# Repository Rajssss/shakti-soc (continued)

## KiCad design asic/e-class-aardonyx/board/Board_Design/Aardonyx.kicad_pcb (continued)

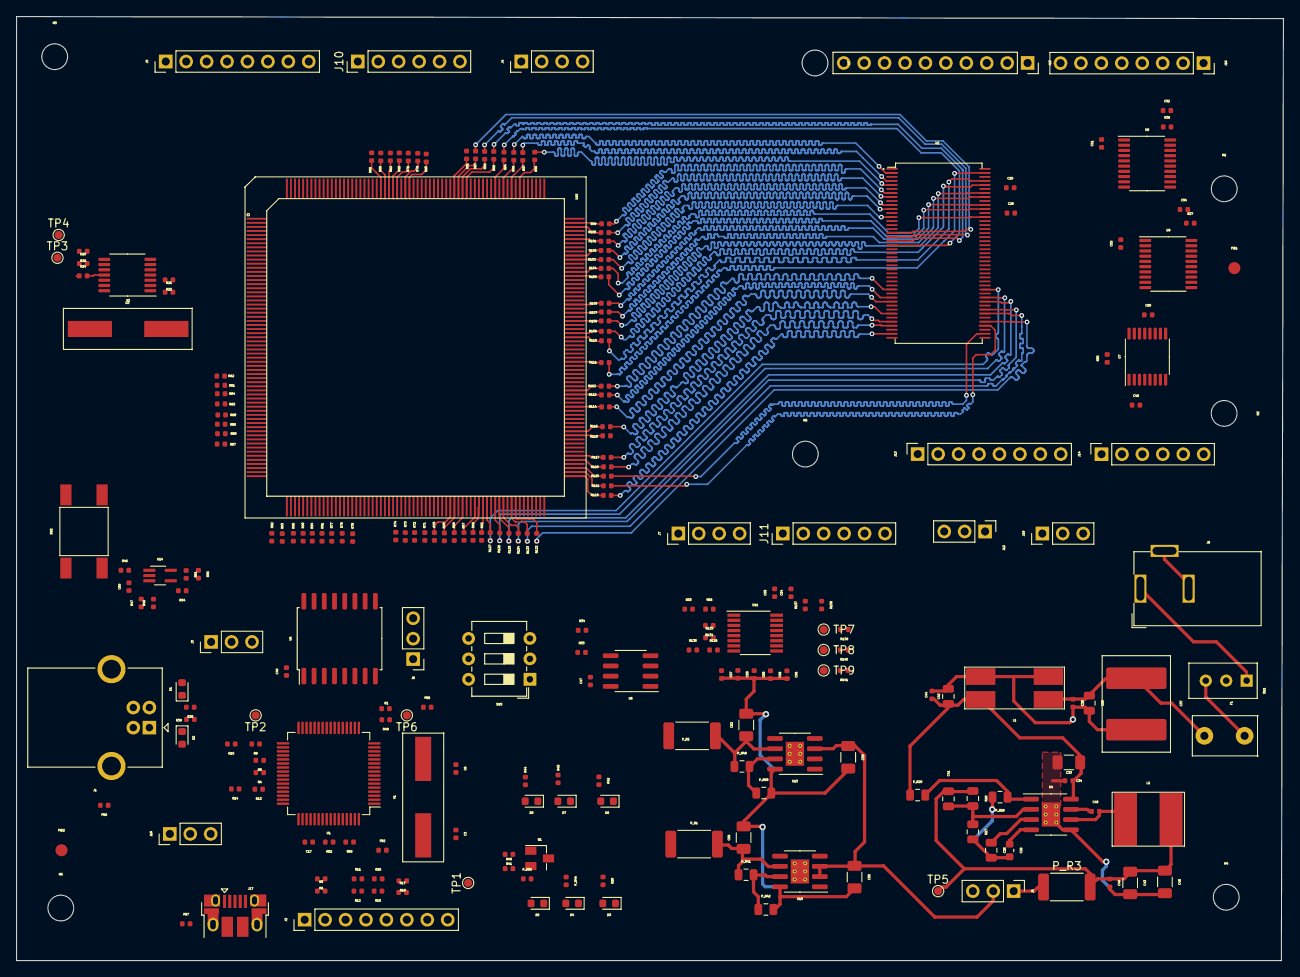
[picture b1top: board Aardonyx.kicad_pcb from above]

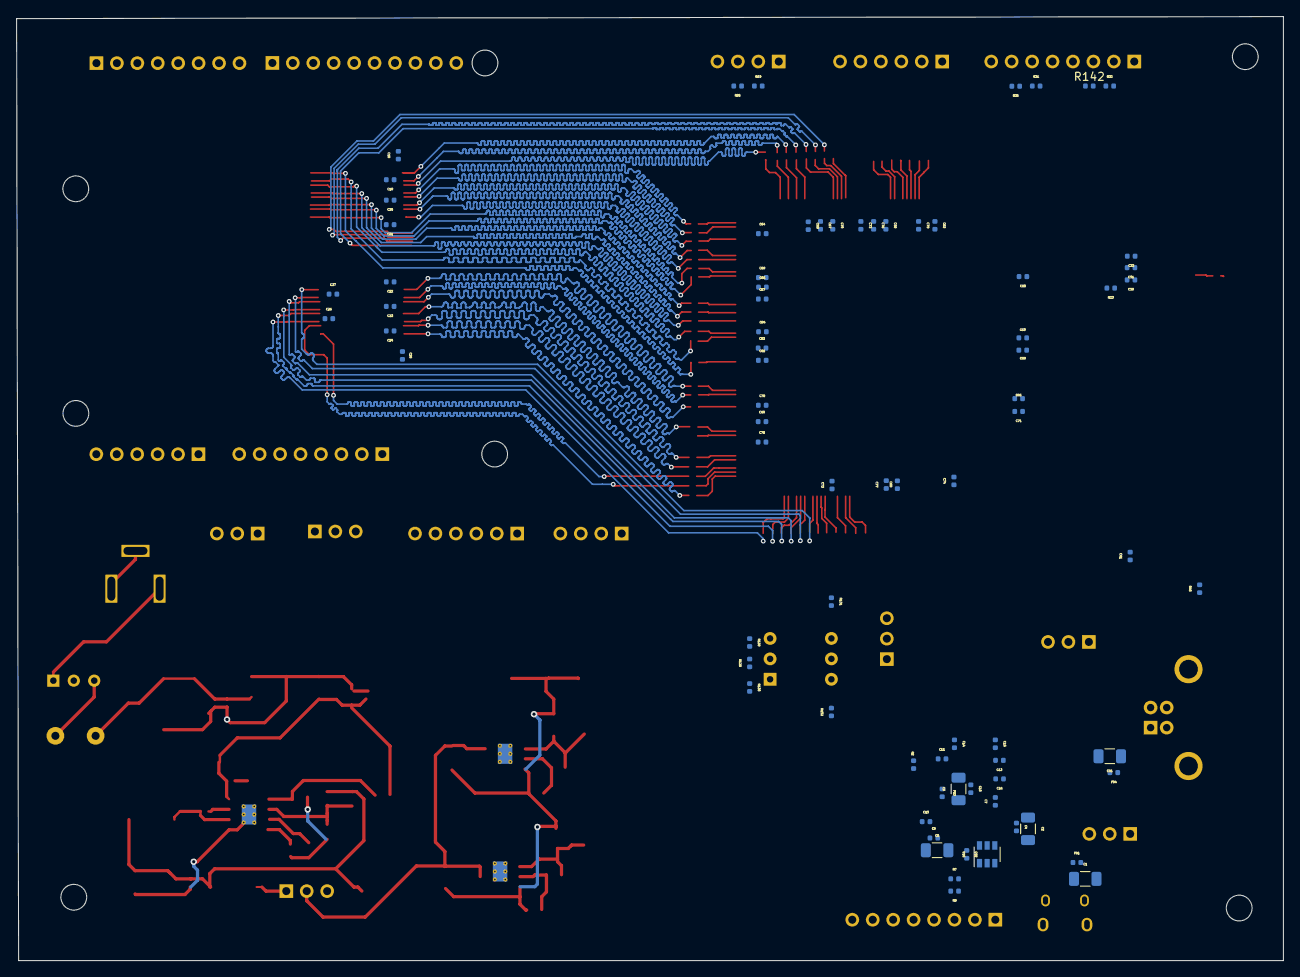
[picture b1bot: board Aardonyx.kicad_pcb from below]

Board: 4 copper layers, 157.5 x 117.3 mm, 325 parts (77 on the bottom side), 287 nets.

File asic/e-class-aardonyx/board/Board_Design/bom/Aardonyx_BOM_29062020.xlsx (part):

Reference | Value | FootPrint | Datasheet | Description | Digikey Part number | Manufaturer Part Number | Manufaturer | Qty
> C3, C6 | 18PF,0402 | Capacitor_SMD:C_0402_1005Metric | https://www.digikey.in/product-detail/en/yageo/CC0201JRNPO9B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 | CAP CER 18PF 50V C0G/NPO 0201 | 311-1386-1-ND | CC0201JRNPO9BN180 | Yageo | 2
> C1, C2, C5, C9, C55, C59, C91 | 4.7UF,1206 | Capacitor_SMD:C_1206_3216Metric | https://www.digikey.in/product-detail/en/kemet/T491A475K016A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 | CAP TANT 4.7UF 10% 16V 1206 | 399-18027-1-ND | T491A475K016AT | Kemet | 7
> C4, C7, C8, C10-C32, C34, C39, C40, C44, C46-C54, C57, C58, C60, C61, C63-C90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 | 0.1UF,0402 | Capacitor_SMD:C_0402_1005Metric | https://www.digikey.in/product-detail/en/avx-corporation/040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 | CAP CER 0.1UF 25V X7R 0402 | 478-10050-1-ND | 04023C104JAT2A | AVX Corporation | 76
> C35, C38, C42 | 1UF,0805 | Capacitor_SMD:C_0805_2012Metric | https://www.digikey.in/product-detail/en/kemet/C0805C105J3RA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 | CAP CER 1UF 25V X7R 0805 | 399-10060-6-ND | C0805C105J3RACTU | Kemet | 3
C36 | 7500PF,0603 | Capacitor_SMD:C_0603_1608Metric | https://www.digikey.in/product-detail/en/kemet/C0603C752J3GA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 | CAP CER 7500PF 25V C0G/NP0 0603 | 399-9980-1-ND | C0603C752J3GAC7867 | Kemet | 1
C37 | 220UF,2924 | Aardonyx:CP_EIA-7260-38_VISHAY_Pad2.68x7.50mm_HandSolder | https://www.digikey.com/product-detail/en/avx-corporation/TC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 | CAP TANT POLY 220UF 25V 2924 | 478-12518-1-ND | TCN4227M025R0100 | AVX Corporation | 1
C41 | 15PF,0805 | Capacitor_SMD:C_0805_2012Metric | https://www.digikey.in/product-detail/en/w%C3%BCrth-elektron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 | CAP CER 15PF 25V C0G/NP0 0805 | 732-7828-1-ND | 885012007029 | Wurth Elektronik | 1
> C33, C43, C45 | 22UF,1206 | Capacitor_SMD:C_1206_3216Metric | https://www.digikey.in/product-detail/en/samsung-electro-mec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 | CAP CER 22UF 25V X5R 1206 | 1276-3047-1-ND | CL31A226KAHNNNE | Samsung Electro-Mechanics | 3
> C56, C62 | 10UF,1206 | Capacitor_SMD:C_1206_3216Metric | https://www.digikey.in/product-detail/en/kemet/C1206C106J3RA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 | CAP CER 10UF 25V X7R 1206 | 399-15734-1-ND | C1206C106J3RACAUTO | KEMET | 2
> D1, D2 | CG0603MLC-12E | Diode_SMD:D_0603_1608Metric | https://www.bourns.com/docs/Product-Datasheets/MLC.pdf | VARISTOR 0603 | CG0603MLC-12ECT-ND | CG0603MLC-12E | Bourns Inc. | 2
> D3-D8 | LED,1206 | LED_SMD:LED_0603_1608Metric | https://www.digikey.com/product-detail/en/lumex-opto-compone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 | LED GREEN DIFFUSED 1206 SMD | 67-1002-1-ND | SML-LX1206GW-TR | Lumex Opto/Components Inc. | 6
F1 | PTCCL13H921DBE | Aardonyx:vishay_ptccl_d1mm_w5mm | https://www.digikey.in/products/en?keywords=PTCCL13H921DBE | PTC RESET FUSE 30V 920MA RADIAL | BC2323-ND | PTCCL13H921DBE | Vishay BC Components | 1
> FB1-FB5 | 600E,FB,0402 | Inductor_SMD:L_0402_1005Metric | https://www.digikey.in/product-detail/en/w%C3%BCrth-elektron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 | FERRITE BEAD 600 OHM 0402 1LN | 732-2388-1-ND | 7427927291 | Wurth Elektronik | 5
> FB6, FB7 | 47E,FB,0402 | Inductor_SMD:L_0402_1005Metric | https://www.digikey.in/product-detail/en/w%C3%BCrth-elektron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 | FERRITE BEAD 47 OHM 0603 1LN | 732-1596-1-ND | 742792608 | Wurth Elektronik | 2
> FID1, FID2 | Fiducial | Fiducial:Fiducial_1.5mm_Mask3mm | ~ |  |  |  |  | 2
> H1-H7 | MountingHole | MountingHole:MountingHole_3.2mm_M3 | ~ |  |  |  |  | 7
J1 | USB_B_6PIN | Connector_USB:USB_B_OST_USB-B1HSxx_Horizontal | https://www.digikey.com/product-detail/en/amphenol-icc-fci/6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 | CONN RCPT USB2.0 TYPEB 4POS R/A | 609-1039-ND | 61729-0010BLF | Amphenol ICC (FCI) | 1
> J2, J9 | Conn_1x8 | Connector_PinHeader_2.54mm:PinHeader_1x08_P2.54mm_Vertical | https://www.digikey.com/products/en?keywords=68000-408HLF | CONN HEADER VERT 8POS 2.54MM | 609-3264-ND | 68000-408HLF | Amphenol ICC (FCI) | 2
> J3, J6, J8, J12, J18, J19 | Conn_1x3_M | Connector_PinHeader_2.54mm:PinHeader_1x03_P2.54mm_Vertical | https://www.digikey.com/product-detail/en/amphenol-icc-fci/6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 | CONN HEADER VERT 3POS 2.54MM | 609-3464-ND | 68000-203HLF | Amphenol ICC (FCI) | 6
> J4, J7 | Conn_1x4 | Connector_PinHeader_2.54mm:PinHeader_1x04_P2.54mm_Vertical | https://www.digikey.com/product-detail/en/amphenol-icc-fci/6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 | CONN HEADER VERT 4POS 2.54MM | 609-3262-ND | 68000-404HLF | Amphenol ICC (FCI) | 2
J5 | PJ-202H PWRJACK | Aardonyx:Pwr_Jack_DC_PJ-202AH_Horizontal | https://www.digikey.com/products/en?keywords=PJ-202AH | CONN PWR JACK 2X5.5MM KINKED PIN | CP-202AH-ND | PJ-202AH | CUI Devices | 1
> J10, J11 | Conn_1x6 | Connector_PinHeader_2.54mm:PinHeader_1x06_P2.54mm_Vertical | https://www.digikey.com/products/en?keywords=68000-406HLF | CONN HEADER VERT 6POS 2.54MM | 609-3263-ND | 68000-406HLF | Amphenol ICC (FCI) | 2
> J13, J16 | Conn_1x8_F | Connector_PinSocket_2.54mm:PinSocket_1x08_P2.54mm_Vertical | https://www.digikey.com/products/en?keywords=%0968685-308LF | CONN RCPT 8POS 0.1 GOLD PCB | 609-3589-ND | 68685-308LF | Amphenol ICC (FCI) | 2
J14 | Conn_1x6_F | Connector_PinSocket_2.54mm:PinSocket_1x06_P2.54mm_Vertical | https://www.digikey.com/product-detail/en/amphenol-icc-fci/7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 | CONN RCPT 6POS 0.1 GOLD PCB | 609-3558-ND | 75915-306LF | Amphenol ICC (FCI) | 1
J15 | Conn_1x10_F | Connector_PinSocket_2.54mm:PinSocket_1x10_P2.54mm_Vertical | https://www.digikey.com/product-detail/en/amphenol-icc-fci/6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 | CONN RCPT 10POS 0.1 GOLD PCB | 609-3584-ND | 68685-310LF | Amphenol ICC (FCI) | 1
J17 | USB_OTG | Connector_USB:USB_Micro-B_Amphenol_10103594-0001LF_Horizontal | https://www.digikey.com/product-detail/en/amphenol-icc-fci/1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 | CONN RCPT USB2.0 MICRO B SMD R/A | 609-4618-1-ND | 10118194-0001LF | Amphenol ICC (FCI) | 1
L1 | CM3421Y600R-10 | Aardonyx:L_Laird_L9.55_W2.84 | https://www.digikey.com/product-detail/en/laird-signal-integ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 | CMC 15A 2LN 60 OHM SMD | 240-2501-1-ND | CM3421Y600R-10 | Laird-Signal Integrity Products | 1
L2 | 3.3UH | Aardonyx:Bourns_srn8040ta_L8.5_W6.6 | https://www.digikey.in/product-detail/en/bourns-inc/SRN8040T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 | FIXED IND 3.3UH 6.6A 15 MOHM SMD | SRN8040TA-3R3YCT-ND | SRN8040TA-3R3Y | Bourns Inc. | 1
> P_R1-P_R3 | 0.02E,2512 | Resistor_SMD:R_2512_6332Metric | https://www.digikey.com/product-detail/en/yageo/PA2512FKF7W0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 | RES 0.002 OHM 1% 2W 2512 | YAG2142CT-ND | PA2512FKF7W0R002E | Yageo | 3
> P_R25, P_R26 | 10KE,0805 | Resistor_SMD:R_0805_2012Metric | https://www.digikey.in/product-detail/en/yageo/RC0805FR-0710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 | RES SMD 10K OHM 1% 1/8W 0805 | 311-10.0KCRCT-ND | RC0805FR-0710KL | Yageo | 2
P_R41 | 169KE,0805 | Resistor_SMD:R_0805_2012Metric | https://www.digikey.com/product-detail/en/panasonic-electron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 | RES 169K OHM 0.1% 1/8W 0805 | P169KDACT-ND | ERA-6AEB1693V | Panasonic Electronic Components | 1
> P_R42, P_R50 | 30.1KE,0805 | Resistor_SMD:R_0805_2012Metric | https://www.digikey.in/product-detail/en/panasonic-electroni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 | RES 30.1K OHM 0.1% 1/8W 0805 | P30.1KDACT-ND | ERA-6AEB3012V | Panasonic Electronic Components | 2
P_R44 | 220E,0402 | Resistor_SMD:R_0402_1005Metric | https://www.digikey.in/product-detail/en/yageo/RC0402FR-0722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 | RES SMD 220 OHM 1% 1/16W 0402 | 311-220LRDKR-ND | RC0402FR-07220RL | Yageo | 1
P_R49 | 78.7KE,0805 | Resistor_SMD:R_0805_2012Metric | https://www.digikey.in/product-detail/en/panasonic-electroni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 | RES 78.7K OHM 0.1% 1/8W 0805 | P78.7KDACT-ND | ERA-6AEB7872V | Panasonic Electronic Components | 1
P_R56 | 120E,0402 | Resistor_SMD:R_0402_1005Metric | https://www.digikey.in/product-detail/en/yageo/RC1206JR-0712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 | RES SMD 120 OHM 1% 1/16W 0402 | 311-120LRCT-ND | RC0402FR-07120RL | Yageo | 1
Q1 | FDN339AN | Package_TO_SOT_SMD:SuperSOT-3 | https://www.digikey.com/product-detail/en/on-semiconductor/F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 | MOSFET N-CH 20V 3A SSOT3 | FDN339ANCT-ND | FDN339AN | ON Semiconductor | 1
R1 | 1KE,0402 | Resistor_SMD:R_0402_1005Metric | https://www.digikey.in/product-detail/en/panasonic-electroni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 | RES SMD 1K OHM 5% 1/10W 0402 | P1.0KJCT-ND | ERJ-2GEJ102X | Panasonic Electronic | 1
R2 | 12KE,0402 | Resistor_SMD:R_0402_1005Metric | https://www.digikey.in/product-detail/en/panasonic-electroni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 | RES SMD 12K OHM 0.1% 1/16W 0402 | P12KDCCT-ND | ERA-2AEB123X | Panasonic Electronic Components | 1
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
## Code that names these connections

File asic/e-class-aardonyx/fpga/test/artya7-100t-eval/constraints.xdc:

## This file is a general .xdc for the Arty A7-100 Rev. D
## To use it in a project:
## - uncomment the lines corresponding to used pins
## - rename the used ports (in each line, after get_ports) according to the top level signal names in the project

## Clock signal
create_clock -period 60.000 -name tck -waveform {0.000 30.000} -add [get_nets pin_tck]

set_multicycle_path -setup 4 -from [get_clocks tck] -to [get_clocks clk_out1_clk_divider] -end
set_multicycle_path -hold 3 -from [get_clocks tck] -to [get_clocks clk_out1_clk_divider] -end
set_multicycle_path -setup 4 -from [get_clocks clk_out1_clk_divider] -to [get_clocks tck] -start
set_multicycle_path -hold 4 -from [get_clocks clk_out1_clk_divider] -to [get_clocks tck] -start

set_property CLOCK_DEDICATED_ROUTE FALSE [get_nets pin_tck_IBUF]
#set_property CLOCK_DEDICATED_ROUTE BACKBONE [get_nets sys_clk_IBUF]

## Switches
set_property -dict { PACKAGE_PIN A8    IOSTANDARD LVCMOS33 } [get_ports { test_mode }]; #IO_L12N_T1_MRCC_16 Sch=sw[0]
set_property -dict { PACKAGE_PIN C11   IOSTANDARD LVCMOS33 } [get_ports { boot_mode[0] }]; #IO_L13P_T2_MRCC_16 Sch=sw[1]
set_property -dict { PACKAGE_PIN C10   IOSTANDARD LVCMOS33 } [get_ports { boot_mode[1] }]; #IO_L13N_T2_MRCC_16 Sch=sw[2]

##Pmod Header JA for JTAG
set_property -dict { PACKAGE_PIN G13   IOSTANDARD LVCMOS33 } [get_ports { pin_tms }]; #IO_0_15 Sch=ja[1]
set_property PULLUP   true [get_ports { pin_tms }]; 
set_property -dict { PACKAGE_PIN B11   IOSTANDARD LVCMOS33 } [get_ports { pin_tdi }]; #IO_L4P_T0_15 Sch=ja[2]
set_property -dict { PACKAGE_PIN D12   IOSTANDARD LVCMOS33 } [get_ports { pin_trst }]; #IO_L6P_T0_15 Sch=ja[4]
set_property PULLDOWN true [get_ports { pin_trst }]; 
set_property -dict { PACKAGE_PIN D13   IOSTANDARD LVCMOS33 } [get_ports { pin_tdo }]; #IO_L6N_T0_VREF_15 Sch=ja[7]
set_property -dict { PACKAGE_PIN B18   IOSTANDARD LVCMOS33 } [get_ports { pin_tck }]; #IO_L10P_T1_AD11P_15 Sch=ja[8]

## Pmod Header JB
set_property -dict { PACKAGE_PIN E15   IOSTANDARD LVCMOS33 } [get_ports { i2c0_sda }]; #IO_L11P_T1_SRCC_15 Sch=jb_p[1]
set_property -dict { PACKAGE_PIN E16   IOSTANDARD LVCMOS33 } [get_ports { i2c0_scl }]; #IO_L11N_T1_SRCC_15 Sch=jb_n[1]
set_property -dict { PACKAGE_PIN D15   IOSTANDARD LVCMOS33 } [get_ports { gpio_14 }]; #IO_L12P_T1_MRCC_15 Sch=jb_p[2]
set_property PULLDOWN true [get_ports { gpio_14 }]; 
set_property -dict { PACKAGE_PIN C15   IOSTANDARD LVCMOS33 } [get_ports { gpio_15 }]; #IO_L12N_T1_MRCC_15 Sch=jb_n[2]
set_property PULLDOWN true [get_ports { gpio_15 }]; 

## Pmod Header JC
set_property -dict { PACKAGE_PIN U12   IOSTANDARD LVCMOS33 } [get_ports { spi1_nss }]; #IO_L20P_T3_A08_D24_14 Sch=jc_p[1]
set_property -dict { PACKAGE_PIN V12   IOSTANDARD LVCMOS33 } [get_ports { spi1_mosi }]; #IO_L20N_T3_A07_D23_14 Sch=jc_n[1]
set_property -dict { PACKAGE_PIN V10   IOSTANDARD LVCMOS33 } [get_ports { spi1_miso }]; #IO_L21P_T3_DQS_14 Sch=jc_p[2]
set_property -dict { PACKAGE_PIN U14   IOSTANDARD LVCMOS33 } [get_ports { spi1_sclk ] }]; #IO_L22P_T3_A05_D21_14 Sch=jc_p[3]

## Pmod Header JD   ISSI QSPI 
set_property -dict { PACKAGE_PIN D4    IOSTANDARD LVCMOS33 } [get_ports { qspi_ncs }]; #IO_L11N_T1_SRCC_35 Sch=jd[1]
set_property -dict { PACKAGE_PIN D3    IOSTANDARD LVCMOS33 } [get_ports { qspi_io[0] }]; #IO_L12N_T1_MRCC_35 Sch=jd[2]
set_property -dict { PACKAGE_PIN F4    IOSTANDARD LVCMOS33 } [get_ports { qspi_io[1] }]; #IO_L13P_T2_MRCC_35 Sch=jd[3]
set_property -dict { PACKAGE_PIN F3    IOSTANDARD LVCMOS33 } [get_ports { qspi_clk }]; #IO_L13N_T2_MRCC_35 Sch=jd[4]
set_property -dict { PACKAGE_PIN H2    IOSTANDARD LVCMOS33 } [get_ports { qspi_io[2] }]; #IO_L15P_T2_DQS_35 Sch=jd[9]
set_property -dict { PACKAGE_PIN G2    IOSTANDARD LVCMOS33 } [get_ports { qspi_io[3] }]; #IO_L15N_T2_DQS_35 Sch=jd[10]

## USB-UART Interface
set_property -dict { PACKAGE_PIN D10   IOSTANDARD LVCMOS33 } [get_ports { uart0_SOUT }]; #IO_L19N_T3_VREF_16 Sch=uart_rxd_out
set_property -dict { PACKAGE_PIN A9    IOSTANDARD LVCMOS33 } [get_ports { uart0_SIN }]; #IO_L14N_T2_SRCC_16 Sch=uart_txd_in

## ChipKit Outer Digital Header
set_property -dict { PACKAGE_PIN V15   IOSTANDARD LVCMOS33 } [get_ports { io7_cell  }]; #IO_L16P_T2_CSI_B_14 Sch=ck_io[0]
set_property PULLDOWN true [get_ports { io7_cell }]; 
set_property -dict { PACKAGE_PIN U16   IOSTANDARD LVCMOS33 } [get_ports { io8_cell  }]; #IO_L18P_T2_A12_D28_14 Sch=ck_io[1]
set_property PULLDOWN true [get_ports { io8_cell }]; 
set_property -dict { PACKAGE_PIN P14   IOSTANDARD LVCMOS33 } [get_ports { io9_cell  }]; #IO_L8N_T1_D12_14 Sch=ck_io[2]
set_property PULLDOWN true [get_ports { io9_cell }]; 
set_property -dict { PACKAGE_PIN T11   IOSTANDARD LVCMOS33 } [get_ports { io10_cell  }]; #IO_L19P_T3_A10_D26_14 Sch=ck_io[3]
set_property PULLDOWN true [get_ports { io10_cell }]; 
set_property -dict { PACKAGE_PIN R12   IOSTANDARD LVCMOS33 } [get_ports { gpio_4  }]; #IO_L5P_T0_D06_14 Sch=ck_io[4]
set_property PULLDOWN true [get_ports { gpio_4 }];
set_property -dict { PACKAGE_PIN T14   IOSTANDARD LVCMOS33 } [get_ports { io12_cell  }]; #IO_L14P_T2_SRCC_14 Sch=ck_io[5]
set_property PULLDOWN true [get_ports { io12_cell }]; 
set_property -dict { PACKAGE_PIN T15   IOSTANDARD LVCMOS33 } [get_ports { io13_cell  }]; #IO_L14N_T2_SRCC_14 Sch=ck_io[6]
set_property PULLDOWN true [get_ports { io13_cell }]; 
set_property -dict { PACKAGE_PIN T16   IOSTANDARD LVCMOS33 } [get_ports { gpio_7 }]; #IO_L15N_T2_DQS_DOUT_CSO_B_14 Sch=ck_io[7]
set_property PULLDOWN true [get_ports { gpio_7 }]; 
set_property -dict { PACKAGE_PIN N15   IOSTANDARD LVCMOS33 } [get_ports { gpio_8  }]; #IO_L11P_T1_SRCC_14 Sch=ck_io[8]
set_property PULLDOWN true [get_ports { gpio_8 }]; 
set_property -dict { PACKAGE_PIN M16   IOSTANDARD LVCMOS33 } [get_ports { io16_cell  }]; #IO_L10P_T1_D14_14 Sch=ck_io[9]
set_property PULLDOWN true [get_ports { io16_cell }]; 
set_property -dict { PACKAGE_PIN V17   IOSTANDARD LVCMOS33 } [get_ports { io17_cell }]; #IO_L18N_T2_A11_D27_14 Sch=ck_io[10]
set_property PULLDOWN true [get_ports { io17_cell }]; 
set_property -dict { PACKAGE_PIN U18   IOSTANDARD LVCMOS33 } [get_ports { io18_cell }]; #IO_L17N_T2_A13_D29_14 Sch=ck_io[11]
set_property PULLDOWN true [get_ports { io18_cell }]; 
set_property -dict { PACKAGE_PIN R17   IOSTANDARD LVCMOS33 } [get_ports { io19_cell }]; #IO_L12N_T1_MRCC_14 Sch=ck_io[12]
set_property PULLDOWN true [get_ports { io19_cell }]; 
set_property -dict { PACKAGE_PIN P17   IOSTANDARD LVCMOS33 } [get_ports { io20_cell }]; #IO_L12P_T1_MRCC_14 Sch=ck_io[13]
set_property PULLDOWN true [get_ports { io20_cell }]; 

## ChipKit Outer Analog Header - as Digital I/O
## NOTE: The following constraints should be used when using these ports as digital I/O.
set_property -dict { PACKAGE_PIN F5    IOSTANDARD LVCMOS33 } [get_ports { spi0_sclk }]; #IO_0_35 Sch=ck_a[0]
set_property -dict { PACKAGE_PIN D8    IOSTANDARD LVCMOS33 } [get_ports { spi0_nss }]; #IO_L4P_T0_35 Sch=ck_a[1]
set_property -dict { PACKAGE_PIN C7    IOSTANDARD LVCMOS33 } [get_ports { spi0_mosi }]; #IO_L4N_T0_35 Sch=ck_a[2]
set_property -dict { PACKAGE_PIN E7    IOSTANDARD LVCMOS33 } [get_ports { spi0_miso }]; #IO_L6P_T0_35 Sch=ck_a[3]

## ChipKit I2C
set_property -dict { PACKAGE_PIN L18   IOSTANDARD LVCMOS33 } [get_ports { i2c1_scl }]; #IO_L4P_T0_D04_14 Sch=ck_scl
set_property -dict { PACKAGE_PIN M18   IOSTANDARD LVCMOS33 } [get_ports { i2c1_sda }]; #IO_L4N_T0_D05_14 Sch=ck_sda

set_property -dict { PACKAGE_PIN C2    IOSTANDARD LVCMOS33 } [get_ports { sys_rst }]; #IO_L16P_T2_35 Sch=ck_rst

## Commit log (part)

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2019-04-18 initial bringup commit
2019-04-18 Generate verilog working
2019-04-18 slight update to Makefile and manager
2019-04-18 Moved the uncore files out to common
2019-04-18 updated fabrics repo until merged
2019-04-26 adding initial files for arty a7 boot
2019-04-26 removing old src folder
2019-04-26 adding new basic SoC
2019-04-26 adding gitignore for artya7-100t
2019-04-26 adding nuke option
2019-04-26 adding makefile targets to generate vivado ips
2019-04-26 ignore vivado generated files and folders
2019-04-26 adding Makefile target for building arty project
2019-04-26 Added top file for FPGA synthesis with DDR3 connections
2019-04-26 changed top to file for synthesis to fpga_top
2019-04-26 adding copy-right and changing module name for Soc
2019-04-26 add fpga_top to file list
2019-04-26 adding clock divider tcl for vivado
2019-04-26 updating IP build target with clock divder generation.
2019-04-26 adding missing exit
2019-04-26 Removed an unused port in fpga_top.v
2019-04-26 renaming constraint files
2019-04-26 fixed version issues
    now the same script can be run on any vivado suite version
2019-04-26 renamed clock divider instance and little formatting of inputs and instance
2019-04-26 adding axi4 clock converter
2019-04-26 changing instance names in fpga_top
2019-04-26 fixed typo
2019-04-27 adding jobs macro for vivado runs
2019-04-27 single parallel launch for all ips
    this will avoiding reloading vivado for each IP
2019-04-27 fixed display statements
2019-04-27 adding comments to scripts
2019-04-27 adding mig ip tcl
2019-04-27 restructure clean targets for Makefile
2019-04-27 simple beautification
2019-04-27 generating instantiation templates for all ips
2019-04-27 import MIG ip
2019-04-27 importing contraints in the project
2019-04-27 generate log files for debugging.
2019-04-27 driving hanging ports
2019-04-27 using variables instead of argument lists
2019-04-27 log only for synthesis and implementation
2019-04-27 removing copy-rights and updating xdc
2019-04-27 drive constants
2019-04-27 use board instead of fpga part
2019-04-27 use board instead of fpga part no
2019-04-27 adding program tcl
2019-04-27 do not hide the command for vivado calls
2019-04-27 setting baud-rate to 19200
2019-04-27 reset to 0
2019-04-27 adding gdb and openocd scripts
2019-04-27 used impl xdc as default for entire process
2019-04-27 Added detailed instructions in README
2019-04-27 Changed the constraints filename
2019-04-27 Changed interface to jlink and added adapter speed parameter in OpenOCD config file
2019-04-27 Added sudo in Makefile for programming the FPGA with the generated bitstream
2019-04-27 Updated README with the step for programming the FPGA
2019-04-27 Added GPIO, PLIC and I2C in SoC
2019-04-29 fixed include paths.
2019-04-29 Added bitstream location and other minor changes
2019-04-29 fetching specific commits instead of masters for all repo
    Will switch to using tags once follow that procedure for all repos.
2019-04-30 updated the docs
2019-04-30 enables should be negated
2019-04-30 number of slaves is 8 not 9
2019-05-03 Added IO master in SoC defines
2019-05-03 Added IO master in SoC
2019-05-03 Changed manager.sh to fetch from master trunk for c-class & devices repo
2019-05-03 Changed MIG interface to 64-bits
2019-05-03 Enabled I cache and D cache
2019-05-21 updated manager to fetch the latest tags of each repo
2019-05-21 included an io_func file for imem and dmem
2019-05-21 rename-translate script added
2019-05-21 Resolve "DDR3 burst mode not working"
2019-06-01 initial push for e-class on arty-a7100t
2019-06-01 reset pc shifted to 0x10 and that's where the debug-halt loop lies
2019-06-01 removing redundant options in bsv-compile
2019-06-01 using latest e-class version 1.2.6
2019-06-04 adding mixedcluster
2019-06-04 removed old includes from Soc
2019-06-04 import relevant types.
2019-06-04 pull latest versions
2019-06-04 interrupts need to be always enabled
2019-06-04 memory mapped done.
    interrupt integration done.
2019-06-04 minimal e-class template
2019-06-06 Added BRAM memory in Soc and SPI constraints
2019-06-06 updated constraints with currently supported ips
2019-06-06 removed DDR interface
2019-06-06 pull latest e-class and latest devices
2019-06-06 fixed eclass instantiation and address map
2019-06-06 commenting out ddr and converter ips
2019-06-06 fixed soc_reset issues
2019-06-06 bumping to 50 MHz
2019-06-06 fixed baud rate for 50MHz operation
2019-06-07 xadc integration working on 35t works with datareg bscan integrated tap
2019-06-12 initial template of aardonyx done
2019-06-12 removing unwanted verilog copy
2019-06-12 removing xadc
2019-06-12 reworded the description
2019-06-13 Support For the artys onboard jtag tap.
    needs a patch on openocd , in process to upstream
2019-06-13 support for c/e bscan 100ttested with upstream
2019-06-19 using rv32imac config.
2019-06-20 Jtag and Arty chains , readme and additional build options
2019-06-22 enabling pmp, counters and triggers
    default target in makefile also updated
2019-06-24 minor README changes
2019-06-24 using latest e-class version
2019-06-24 updated memory map
2019-06-29 integrating sdram-32bit
2019-06-29 sending reset pc as soc argument
2019-06-29 updating e-class and device versions
2019-07-01 top level verilog added
2019-07-01 update devices with new qspi changes
2019-07-01 renamed qspi io interface names
2019-07-01 fixed io constraints
2019-07-01 copy aardonyx into new verilog folder
2019-07-01 update top module info
2019-07-02 fixed qspi pin mapping
2019-07-04 fix: enable signals for sdram are only 4 bits wide
2019-07-05 adding hanging input for test-mode enable/disable
2019-07-08 updating devices for e-class to 3.5.2
2019-07-08 use 32-bit toolchain
2019-07-08 updating e-class to latest version
2019-07-18 increasing gpio number to 32
2019-07-19 updating devices to 3.6.0
    sdram latch issues fixed
2019-07-20 updating e-class version
2019-07-23 updating to new e-class
2019-07-25 Resolve "e-class-mukut"
2019-07-26 Support for the e-class on 35t with the integrated debugger
    and seperate make target to build mcs file
2019-07-30 adding pre-built MCS
2019-07-30 adding pre-built mcs for e-class-100t
2019-07-30 adding pre-built mcs for eclass-35t
2019-08-06 fixed tcl for pre-built mcs files
2019-08-06 close #19
2019-08-06 fixed typo. related to #19
2019-08-07 close #20
2019-08-08 extending more GPIOs
2019-08-08 extending gpios to 32-bits
2019-08-09 close #24
2019-08-09 more fixes related to #25
2019-08-09 updated the e-class 100t with latest build
2019-08-09 updated 35t port with new mcs file
2019-08-10 adding auto mcs generation from cicd
2019-08-10 Renamed ci file
2019-08-10 fixed script name
2019-08-10 updating readme to use the artifacts
2019-08-10 redirecting to artifacts for pre-built mcs files
2019-08-10 fixed 100t build script
2019-08-10 fixed issue with bscan2e being disabled
2019-08-16 fixed fpga_top for more gpios
2019-08-16 fixed fpga_top wire width. allow rebuilding hierarchy
2019-08-19 updating e-class version on all platforms.
2019-08-20 removing obsolete mcs files
2019-08-20 adding support for ac701
2019-08-23 run ci on all changes under boards directory. This is to ensure each mcs artifact is available in the latest build
2019-08-23 run ci-cd on every commit to master
2019-08-23 fixed indentation
2019-08-23 udpated readme for 35-t
2019-08-23 Aardonyx pinmux
2019-08-24 fixed io interface name for qspi
2019-08-24 fixed qspi instance and io naming
2019-08-26 Fixed wget command to change the downloaded file name
    close issue #29
2019-09-01 moving bootrom outside SoC
2019-09-09 instantiating bootrom at aardonyx level.
2019-09-10 BRAM module no longer required
2019-09-11 connected interrupt from plic to e-class
2019-09-12 fixed port mapping
2019-09-16 removing all ext_interrupts
2019-09-16 bumping to latest modules
2019-09-16 remove all files after build
2019-09-17 updated arty to latest c-class
2019-09-17 updating to latest i2c
2019-09-18 connecting sdram to fabrics
2019-09-20 updating memory map in README
2019-09-24 moved to new bram type
2019-09-25 Resolve "Adding verification repository for e-class-aardonyx"
2019-10-23 adding nexysvideo source files
2019-10-24 changing memory map to accomodate CLIC
2019-11-21 Resolve "boot code for aardonyx"
2019-11-21 Resolve "verify-eclass-changing-mkreg-to-mkrega"
2019-11-21 Resolve "Adding test cases for peripherals"
2019-11-21 fixed verilog define issue in vivado
2019-11-22 no pmp support on 35t
2019-11-22 Resolve "Job Failed #357270513"
2019-11-29 Added SPI and QSPI flash connections
2019-12-02 adding wrapper files
2019-12-02 Adding test_bench for wrappers
2019-12-02 updated constraints file
2019-12-03 updates_to_the_testbench
2019-12-03 Updating fpga_top.v
2019-12-03 Resolve "aardonyx fpga fixes"
2019-12-04 Renaming inputs outputs
2019-12-04 adding sdram_wrapper,updating aardonyx wrapper and test bench
2019-12-04 Added QSPI and SPI connections
2019-12-04 Cypress and ISSI verilog wrappers
2019-12-04 Connecting sdram io_interface
2019-12-05 changes for tck and trst
2019-12-05 Modified link_irun
2019-12-05 Resolve "fix for arty fpga"
2019-12-05 renamed issi bsv wrapper; modified SDRAM data line connections; changes in link_irun
2019-12-06 updating sim_config
2019-12-06 inverting outen signals of sdram in aardonyx_wrapper.v
2019-12-06 changes in boot option
2019-12-07 Adding boot code for simulation as QSPI BFM initial wait is different in simulation
2019-12-07 Modified MemoryEnd for simulation
2019-12-08 Reverted the out enable changes in aardonyx_wrapper; changes in SDRAM data line connections
2019-12-08 Initial commit for the peripheral tests
2019-12-10 Adding I2C to the tetbench
2019-12-10 negating gpio signals for pinmux pins
2019-12-10 negating gpio outen signals of pinmux pins
2019-12-10 adding .so files for openocd support
2019-12-10 enable openocd
2019-12-11 Test codes for i2c
2019-12-12 Resolve "pinmux fix"
2019-12-12 adding testbench for uart1
2019-12-12 Modified PLIC input
2019-12-12 Verified SPI connected to Pinmux
2019-12-15 Driver code for UART with pinmux configuration
2019-12-15 Connections for pinmux UARTs
2019-12-16 Drivers for PWM verification
2019-12-16 gpio test code
2019-12-16 read gpio code
2019-12-16 updated pull down pads for gpio and atpg changes
2019-12-17 Adding I2C tests
2019-12-17 removing I2C_tests from main folder
2019-12-17 merging wrapper_sim config into synth macro itself
2019-12-17 Resolve "dtvec fix for e-class"
2019-12-17 reverting 35t devices version to fit within fpga. Async resets have created an issue
2019-12-19 Modified the default value of UART RX pin
2019-12-25 Resolve "uart interrupt feature"
2020-01-16 Resolve "aardonyx wrapper testbench changes"
2020-01-24 Use vivado_lab in case vivado is not present
    vivado_lab is free and can be used by developers to program
    the target.
2020-01-27 Resolve "e-class fpga with devices update"
2020-02-28 Resolve "revamping shakti-soc"
2020-03-09 updare
2020-03-17 Patch 1
2020-04-07 update bom
2020-04-15 update footprint
2020-04-15 footprint update
2020-04-15 updated BOM
2020-04-21 updated commented schematics
2020-04-21 updated footprint for netlist
2020-04-23 updated footprint
2020-04-27 updated the schematics in pdf
2020-05-14 Updated footprint association
2020-05-14 update pending footprint
2020-05-19 add component placing
2020-05-22 update pec & footprint
2020-05-25 update component placement
2020-05-27 update foot print & componenet placement
2020-06-01 Changes done for VCC symbol issue
2020-06-02 update component palcement comment by kottee
2020-06-04 add skt sock footprint & componont update
2020-06-05 update component place
2020-06-08 Placement changes
2020-06-08 updated compo placement
2020-06-12 add bom
2020-06-13 Updated few components
2020-06-15 Updating BOM
2020-06-15 update footprint & bom
2020-06-17 updated component
2020-06-17 add aardonyx_bom
2020-06-19 updated the component
2020-06-23 pcb size minimised
2020-06-24 minimize pcb size
2020-06-25 Replacing ADM1085 with ADM1186
2020-06-26 Updating footprint for test points
2020-06-26 add bom & updated component
2020-06-27 Updating placements
2020-06-29 Updating 1x6 connector
2020-06-29 updated track placement
2020-07-02 udated track
2020-07-03 removing incore license
2020-07-04 pcb updates
2020-07-06 update track laying
2020-07-06 using uart_v2 in c-class on 100t
